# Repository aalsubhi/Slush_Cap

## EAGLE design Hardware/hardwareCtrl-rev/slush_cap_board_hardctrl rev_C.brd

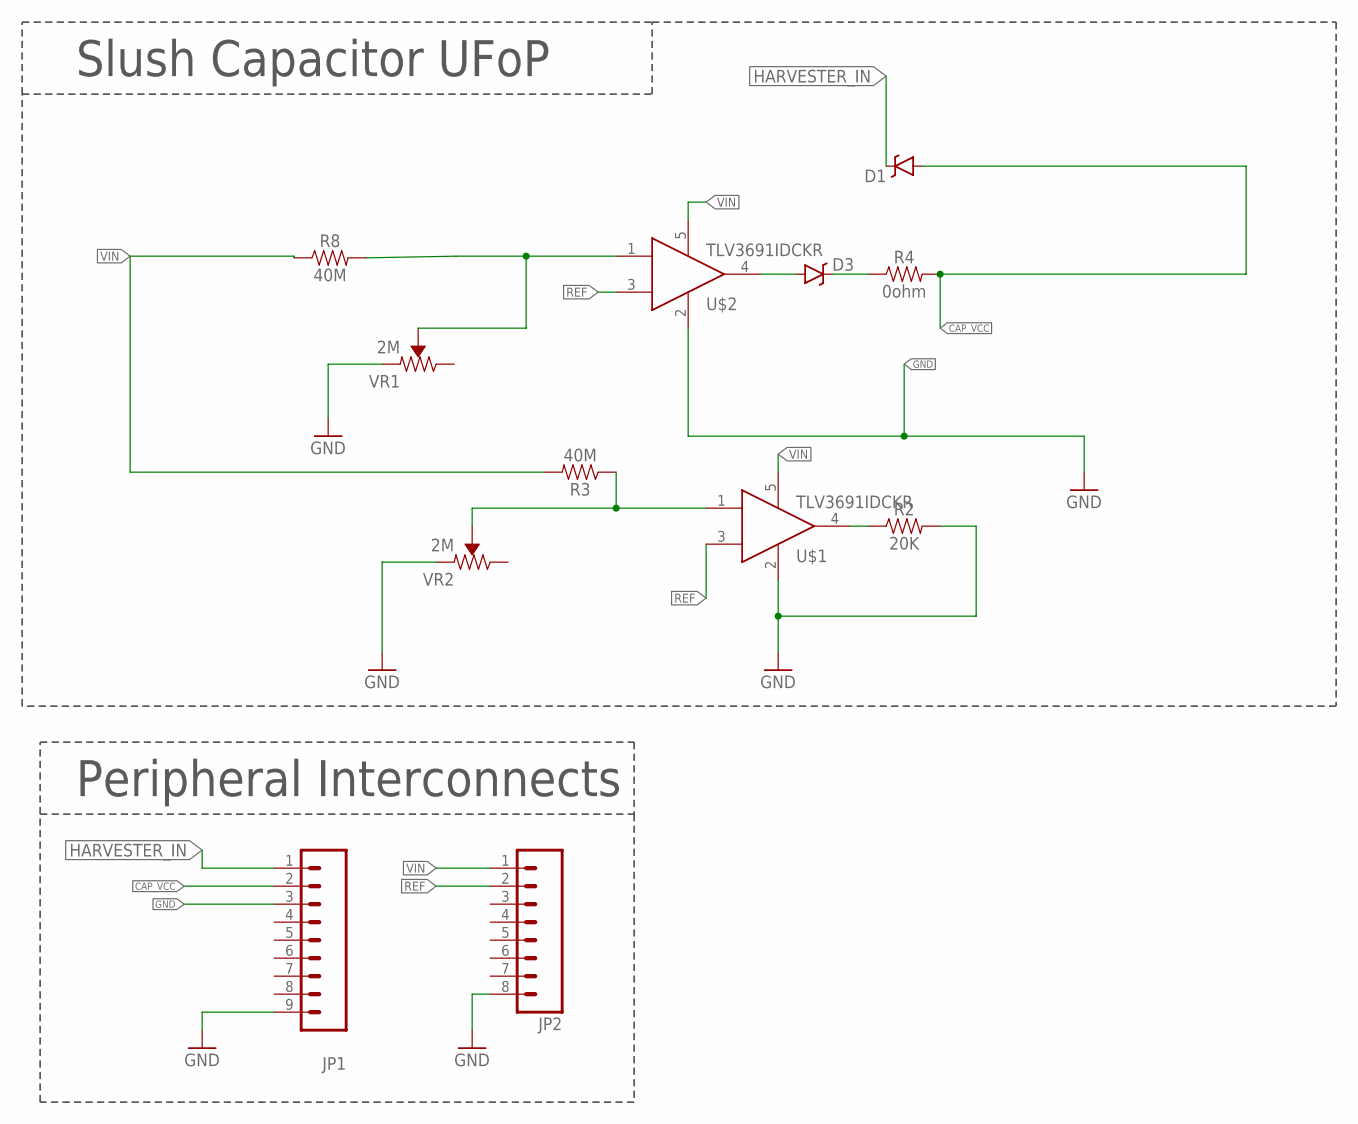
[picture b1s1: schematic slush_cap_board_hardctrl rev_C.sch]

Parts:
D1, D3: RB751; SOD-523; MPN BAS40-02V-V-G-08; DIGIKEY BAS40-02V-V-G-08GICT-ND
JP1: M091.27MM; 1X09-1.27MM; MANUFACTURERPARTNUMBER GRPB091VWVN-RC; DIGIKEY S9014E-09-ND
JP2: M081.27MM; 1X08-1.27MM; MANUFACTURERPARTNUMBER GRPB081VWVN-RC; DIGIKEY S9014E-08-ND
R2: 20K; 0805
R3, R8: 40M; 0805
R4: 0ohm; 0603
U$1, U$2: TLV3691IDCKR; SOT353
VR1, VR2: 2M; TRIMPOT-SMD-3MM-CLOSED

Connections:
CAP_VCC: D1.A, JP1.2, R4.2
GND: JP1.3, JP1.9, JP2.8, R2.2, U$1.2, U$2.2, VR1.1 (CCW), VR2.1 (CCW)
HARVESTER_IN: D1.C, JP1.1
unnamed: D3.A, U$2.4
unnamed: R2.1, U$1.4
unnamed: R8.2, U$2.1, VR1.2 (WIPER)
unnamed: R3.1, U$1.1, VR2.2 (WIPER)
unnamed: D3.C, R4.1
REF: JP2.2, U$1.3, U$2.3
VIN: JP2.1, R3.2, R8.1, U$1.5, U$2.5

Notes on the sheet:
Peripheral Interconnects
Slush Capacitor UFoP

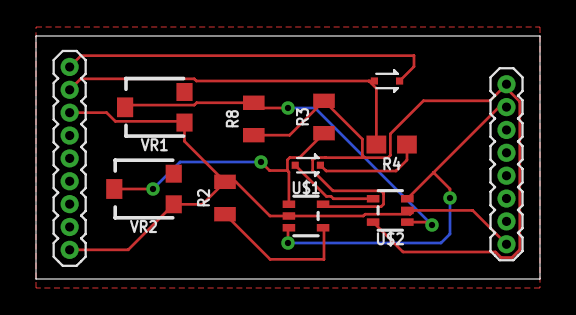
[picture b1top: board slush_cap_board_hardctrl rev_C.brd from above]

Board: 2 copper layers, 28.0 x 13.5 mm, 12 parts (0 on the bottom side), 10 nets.

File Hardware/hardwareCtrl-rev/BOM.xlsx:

Part | Value | Package | Description | Mouser #:
D1 |  | SOD-523 | Schottky diodes | 78-BAS40-02V-V-G-08
D3 |  | SOD-523 | Schottky diodes | 78-BAS40-02V-V-G-08
JP1 |  | 1X09-1.27MM | Header 9
JP2 |  | 1X08-1.27MM | Header 8
R2 | 20K | 805 | resistor
R3 | 40M | 805 | resistor
R4 | 0ohm | 603 | resistor
R8 | 40M | 805 | resistor
U$1 | TLV3691IDCKR | SOT353 | comparetor | 595-TLV3691IDCKR
U$2 | TLV3691IDCKR | SOT353 | comparetor | 595-TLV3691IDCKR
VR1 | 2M | TRIMPOT-SMD-3MM-CLOSED | Trimming Potentiometer (Trimpot) | 652-3313J-1-205E
VR2 | 2M | TRIMPOT-SMD-3MM-CLOSED | Trimming Potentiometer (Trimpot) | 652-3313J-1-205E

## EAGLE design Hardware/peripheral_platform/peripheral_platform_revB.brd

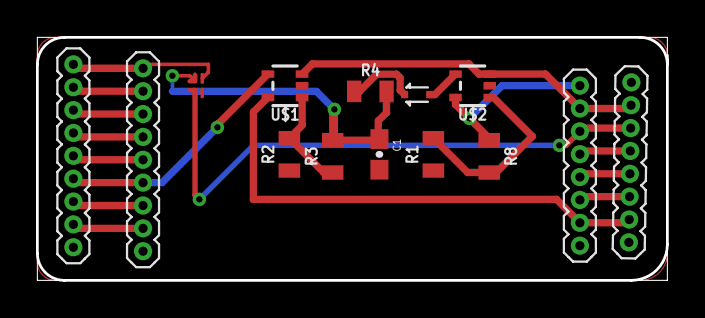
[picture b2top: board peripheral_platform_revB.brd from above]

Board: 2 copper layers, 35.0 x 13.5 mm, 14 parts (0 on the bottom side), 21 nets.

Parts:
C1: 0603-CAP
D3: RB751; SOD-523
JP1, JP3: 1X09-1.27MM
JP2, JP4: 1X08-1.27MM
R1, R2, R3, R8: ?M; 0805
R4: ?K; 0805
U5: SLG59M1557V; 4STDFN
U$1, U$2: TLV3691IDCKR; SOT353

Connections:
GATE: JP1.1, JP3.1, U5.1
GND: C1.2, JP1.9, JP2.8, JP3.9, JP4.8, R1.1, R2.1, U5.4, U$1.2, U$2.2
INT: JP1.6, JP3.6, U$1.4
unnamed: D3.A, U$2.4
unnamed: JP1.4, JP3.4
unnamed: JP1.2, JP3.2
unnamed: R1.2, R8.2, U$2.1
unnamed: R2.2, R3.1, U$1.1
unnamed: JP1.5, JP3.5
unnamed: JP1.7, JP3.7
unnamed: JP1.8, JP3.8
unnamed: JP2.4, JP4.4
unnamed: JP2.5, JP4.5
unnamed: JP2.6, JP4.6
unnamed: JP1.3, JP3.3
unnamed: D3.C, R4.1
unnamed: C1.1, R3.2, R4.2, U5.2
PERIPHERAL_VCC: JP2.3, JP4.3, U5.3
REF: JP2.2, JP4.2, U$1.3, U$2.3
VCC: JP2.7, JP4.7, U$1.5
VIN: JP2.1, JP4.1, R8.1, U$2.5

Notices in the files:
parts and their libraries:
SparkFun-DiscreteSemi: Licensing: CC v3.0 Share-Alike You are welcome to use this library for commercial purposes.
SparkFun-Connectors: Licensing: Creative Commons ShareAlike 4.0 International - https://creativecommons.org/licenses/by-sa/4.0
